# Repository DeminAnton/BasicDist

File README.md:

# Analog Distortion Pedal – Design and Simulation

Welcome to the repository for the analog distortion pedal.  
This project combines circuit design and simulation.

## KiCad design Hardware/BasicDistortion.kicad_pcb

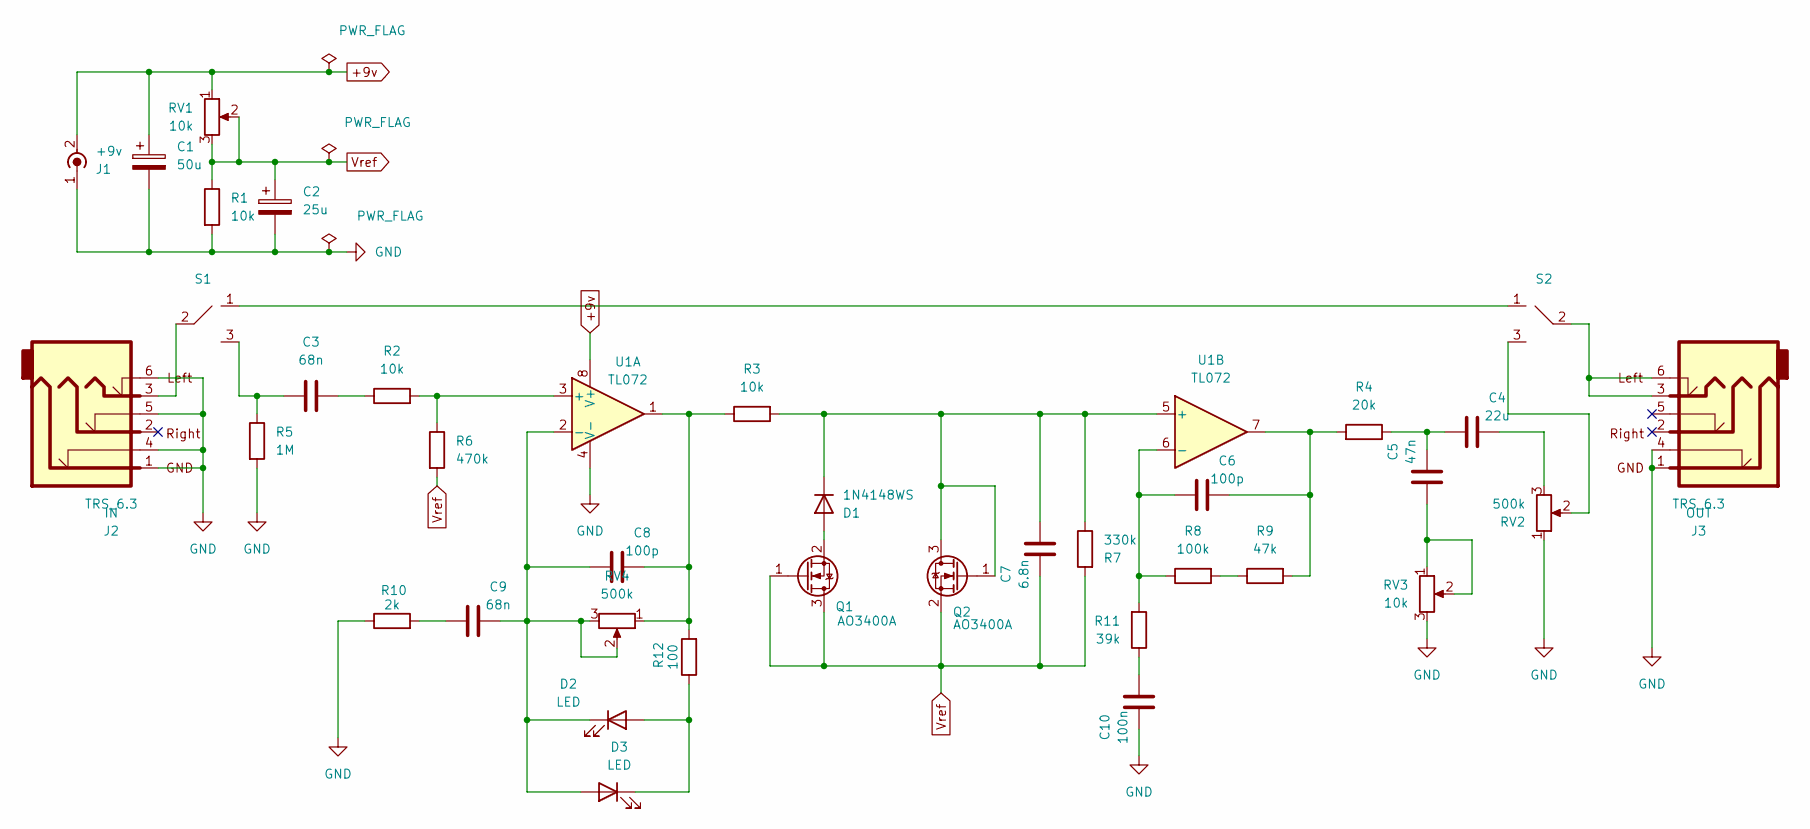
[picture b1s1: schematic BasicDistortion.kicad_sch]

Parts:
C1: 50u; CP_Radial_D8.0mm_P3.50mm
C2: 25u; CP_Radial_D6.3mm_P2.50mm
C3, C9: 68n; C_Rect_L10.0mm_W4.0mm_P7.50mm_MKS4
C4: 22u; CP_Radial_D6.3mm_P2.50mm
C5: 47n; C_Rect_L10.0mm_W4.0mm_P7.50mm_MKS4
C6, C8: 100p; C_0805_2012Metric
C7: 6.8n; C_Rect_L10.0mm_W4.0mm_P7.50mm_MKS4
C10: 100n; C_Rect_L10.0mm_W4.0mm_P7.50mm_MKS4
D1: 1N4148WS; D_SOD-323
D2, D3: LED; LED_D4.0mm
J1: +9v; PinSocket_1x02_P2.00mm_Vertical
J2: IN; TRS_6.3
J3: OUT; TRS_6.3
Q1, Q2: AO3400A; SOT-23
R1, R2, R3: 10k; R_0805_2012Metric
R4: 20k; R_0805_2012Metric
R5: 1M; R_0805_2012Metric
R6: 470k; R_0805_2012Metric
R7: 330k; R_0805_2012Metric
R8: 100k; R_0805_2012Metric
R9: 47k; R_0805_2012Metric
R10: 2k; R_0805_2012Metric
R11: 39k; R_0805_2012Metric
R12: 100; R_0805_2012Metric
RV1: 10k; Potentiometer_Bourns_3296W_Vertical
RV2, RV4: 500k; Pot_old_vert
RV3: 10k; Pot_old_vert
S1, S2: 1PDT
U1: TL072; SOIC-8_3.9x4.9mm_P1.27mm

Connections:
+9v: C1.1, J1.2 (Ext), RV1.1, U1.8 (V+)
GND: C1.2, C2.2, C10.2, J1.1 (In), J2.1, J2.4, J2.5, J2.6, J3.1, J3.4, R1.2, R5.2, R10.1, RV2.1, RV3.3, U1.4 (V-)
unnamed: C3.1, R5.1, S1.3
unnamed: C3.2, R2.1
unnamed: C4.1, C5.2, R4.1
unnamed: C4.2, RV2.3
unnamed: C5.1, RV3.1, RV3.2
unnamed: C6.2, R4.2, R9.2, U1.7
unnamed: C8.2, R3.1, R12.2, RV4.1, U1.1
unnamed: C9.1, R10.2
unnamed: C10.1, R11.1
unnamed: D1.2 (A), Q1.2 (S)
unnamed: C7.1, D1.1 (K), Q2.1 (G), Q2.3 (D), R3.2, R7.1, U1.5 (+)
unnamed: D2.2 (A), D3.1 (K), R12.1
unnamed: C8.1, C9.2, D2.1 (K), D3.2 (A), RV4.2, RV4.3, U1.2 (-)
unnamed: J2.3, S1.2
unnamed: J3.3, J3.6, S2.2
unnamed: R8.2, R9.1
unnamed: RV2.2, S2.3
unnamed: S1.1, S2.1
unnamed: R2.2, R6.1, U1.3 (+)
unnamed: C6.1, R8.1, R11.2, U1.6 (-)
Vref: C2.1, C7.2, Q1.1 (G), Q1.3 (D), Q2.2 (S), R1.1, R6.2, R7.2, RV1.2, RV1.3

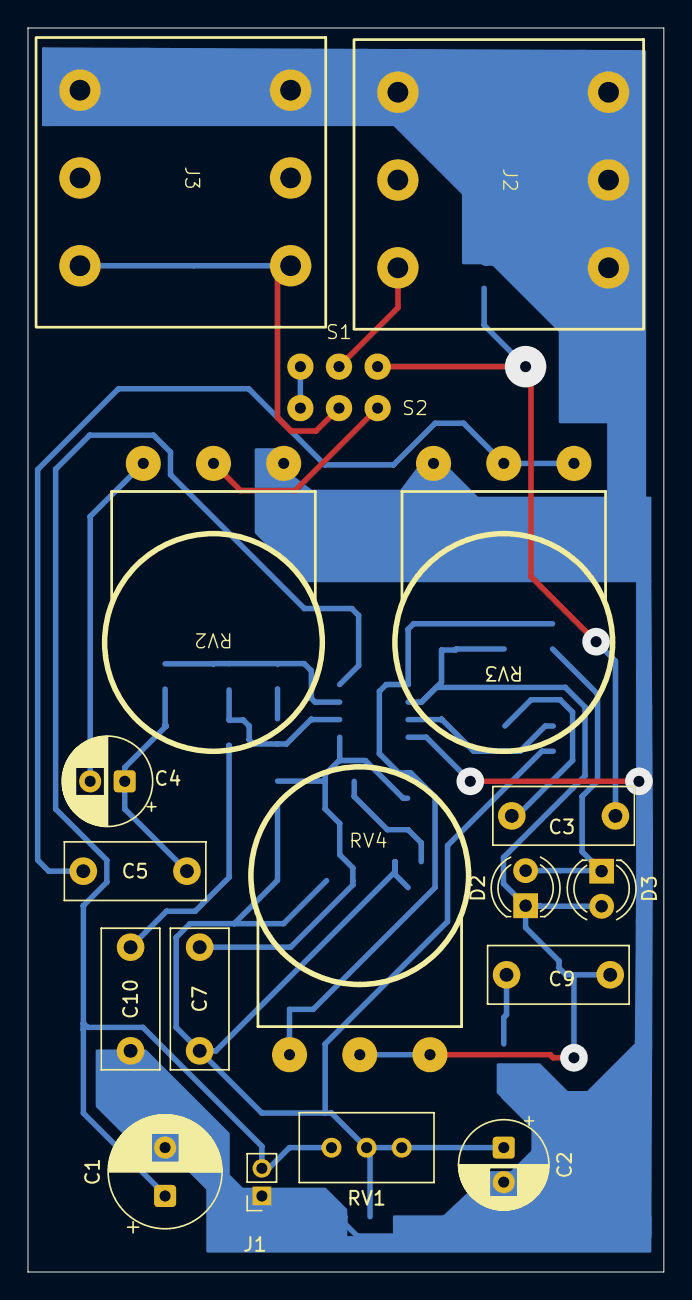
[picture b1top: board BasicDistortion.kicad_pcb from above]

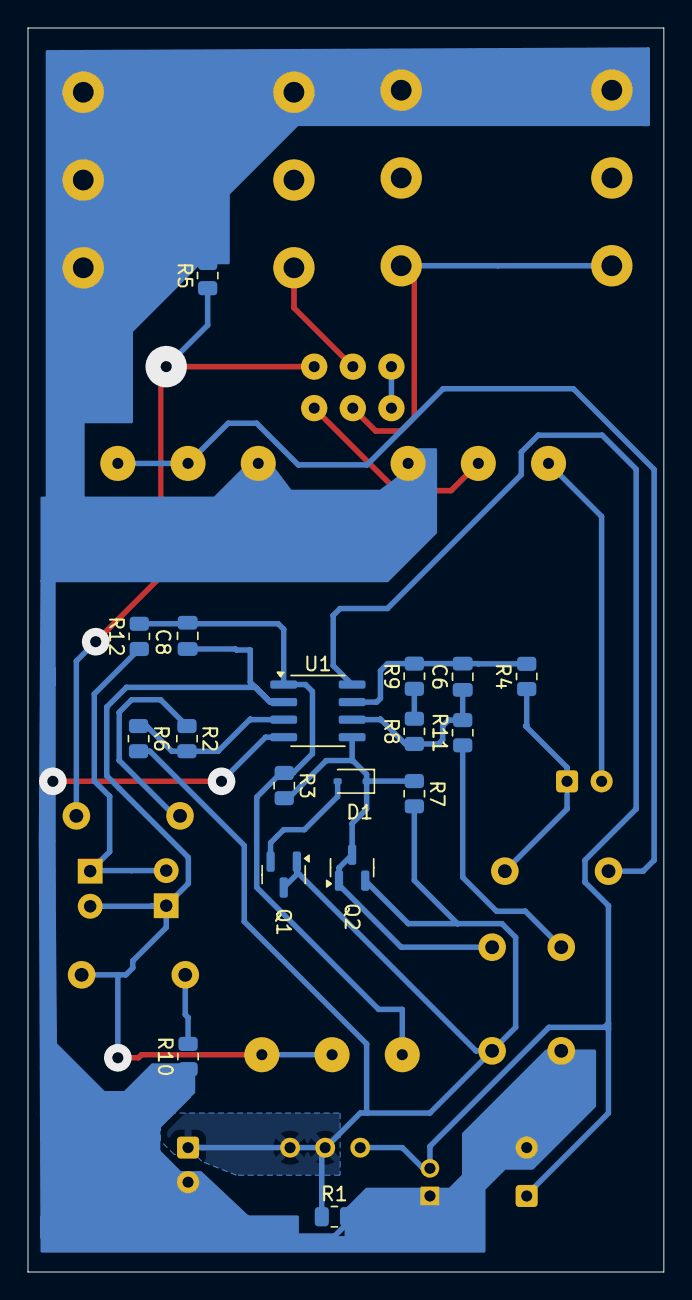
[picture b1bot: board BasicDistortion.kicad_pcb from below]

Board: 2 copper layers, 46.0 x 90.0 mm, 37 parts (18 on the bottom side), 23 nets.

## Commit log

2025-07-02 Check readme
